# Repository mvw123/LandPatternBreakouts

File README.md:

Work in progress - LandPatternBreakouts
====================

Land Pattern Breakout board 
Drawn in Eagle 6.5.0

CAD A (WIP)
================
Work in progress
not produced or tested yet.
These land pattern breakouts are intended to be non-specific to any particular chips, meaning they are just intended to breakout a particular type of footprint.

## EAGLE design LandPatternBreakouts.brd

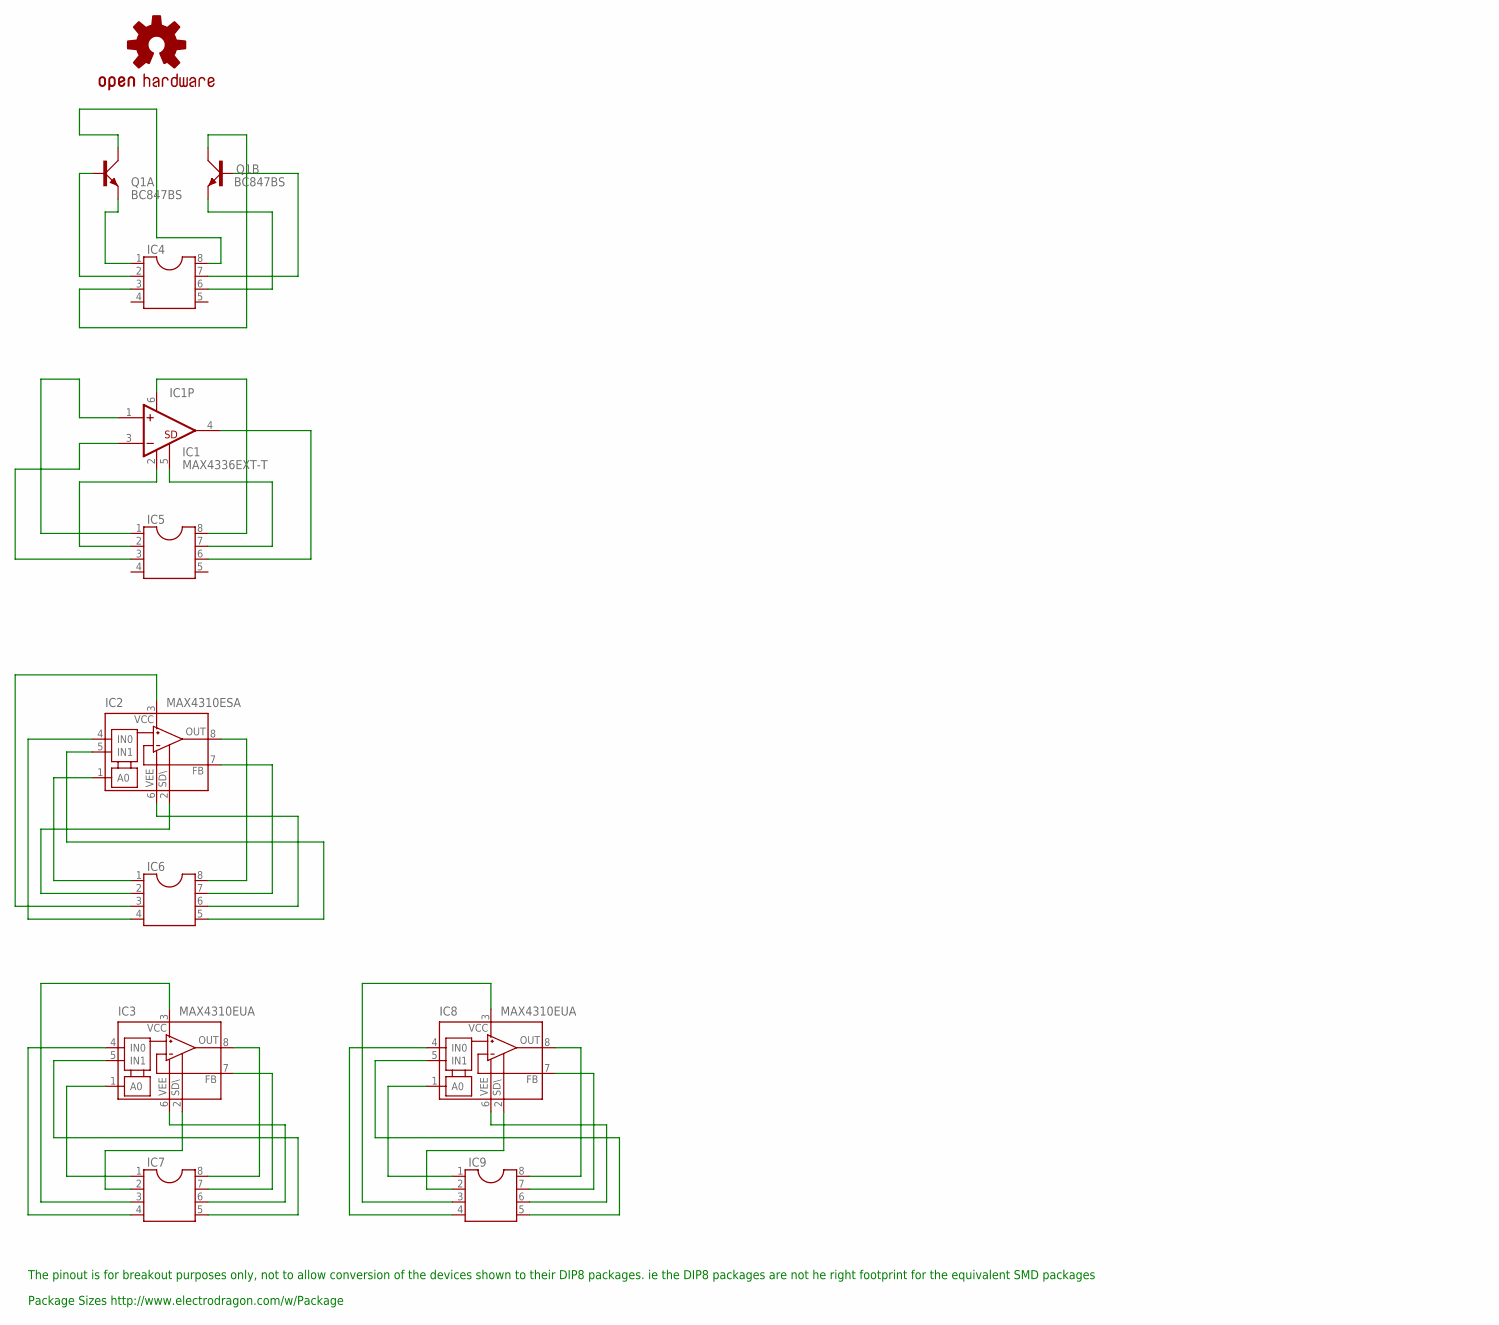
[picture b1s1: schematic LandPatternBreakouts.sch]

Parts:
IC1: MAX4336EXT-T; SOT23-6L
IC2: MAX4310ESA; UMAX8
IC3, IC8: MAX4310EUA; SO08
IC4, IC5, IC6, IC7, IC9: DIL8; DIL08
LOGO1: OSHW-LOGOS; OSHW-LOGO-S
Q1: BC847BS; SOT363_PHILIPS

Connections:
unnamed: IC1.1 (+IN), IC5.1
unnamed: IC1.2 (V-), IC5.2
unnamed: IC1.3 (-IN), IC5.3
unnamed: IC1.4 (OUT), IC5.6
unnamed: IC1.6 (V+), IC5.8
unnamed: IC2.1 (A0), IC6.1
unnamed: IC2.2 (!SHDN), IC6.2
unnamed: IC1.5 (SHUTDOWN), IC5.7
unnamed: IC2.3 (V+), IC6.3
unnamed: IC2.4 (IN0), IC6.4
unnamed: IC2.5 (IN1), IC6.5
unnamed: IC2.6 (V-), IC6.6
unnamed: IC2.7 (FB), IC6.7
unnamed: IC2.8 (OUT), IC6.8
unnamed: IC3.4 (IN0), IC7.4
unnamed: IC3.2 (!SHDN), IC7.2
unnamed: IC3.3 (V+), IC7.3
unnamed: IC3.5 (IN1), IC7.5
unnamed: IC3.6 (V-), IC7.6
unnamed: IC3.7 (FB), IC7.7
unnamed: IC3.8 (OUT), IC7.8
unnamed: IC3.1 (A0), IC7.1
unnamed: IC4.8, Q1.6 (C)
unnamed: IC4.2, Q1.2 (B)
unnamed: IC4.1, Q1.1 (E)
unnamed: IC4.6, Q1.4 (E)
unnamed: IC4.3, Q1.3 (C)
unnamed: IC4.7, Q1.5 (B)
unnamed: IC8.2 (!SHDN), IC9.2
unnamed: IC8.3 (V+), IC9.3
unnamed: IC8.4 (IN0), IC9.4
unnamed: IC8.5 (IN1), IC9.5
unnamed: IC8.6 (V-), IC9.6
unnamed: IC8.7 (FB), IC9.7
unnamed: IC8.8 (OUT), IC9.8
unnamed: IC8.1 (A0), IC9.1

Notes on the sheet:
Package Sizes http://www.electrodragon.com/w/Package
The pinout is for breakout purposes only, not to allow conversion of the devices shown to their DIP8 packages. ie the DIP8 packages are not he right footprint for the equivalent SMD packages

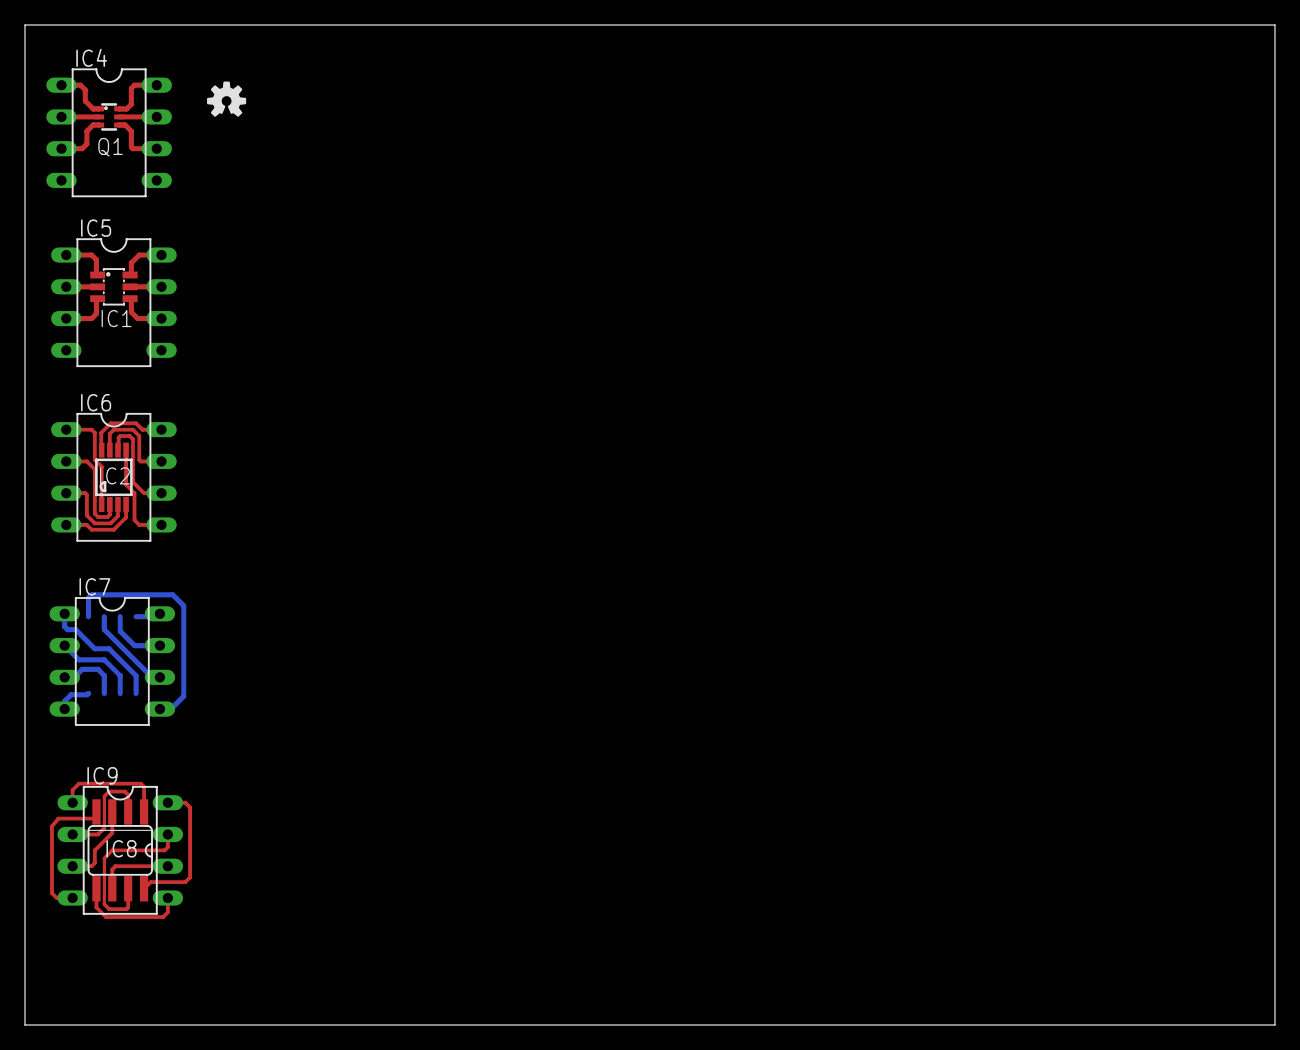
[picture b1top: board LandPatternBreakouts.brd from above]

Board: 2 copper layers, 100.0 x 80.0 mm, 11 parts (1 on the bottom side), 36 nets.

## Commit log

2014-09-30 Land Pattern Breakouts
    Land Pattern Breakouts. First commit is mainly SC70, SOT23 to DIP8
    breakout. These are NOT adapters, just breakouts
2014-12-31 No Known changes
    No Known changes
2015-09-18 updated comments
2015-09-18 added Work in progress -
2016-01-15 no updates
    no updates
2017-09-25 DS store updates

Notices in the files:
parts and their libraries:
SparkFun-Aesthetics: Licensing: Creative Commons ShareAlike 4.0 International - https://creativecommons.org/licenses/by-sa/4.0
